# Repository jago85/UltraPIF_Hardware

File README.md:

# UltraPIF_Hardware
The UltraPIF is a replacement for the N64 PIF-NUS chip.

The PIF-NUS chip responsible for region lockout and copy protection. But it also has essential features like game controller access, cartridge EEPROM access and it includes the MIPS CPU boot rom.

The UltraPIF can replace all functions of the original PIF, but ignores the CIC and thus enables a region-free N64. In addition the UltraPIF comes with an integrated clock generator to compensate the differences of the video clocks for NTSC and PAL consoles. The UltraPIF includes an SPI NOR FLASH used to store the N64 software images. At the moment the FLASH is 16 MiB in size and 99% empty, so there could be features like backup and restore of savegame data or even direct emulation of SI (serial interface) hardware (ControllerPak, cart EEPROM, RTC). An RGB LED replaces the original N64 power LED and is used to show if the N64 is running in NTSC or PAL mode. The color is user programmable.

The project consists of custom PCBs, an FPGA design, an MCU firmware and a bunch of software for the N64 itself.

In this repository you find the KiCad hardware files.

You can find hints for assembly and installation in [the wiki](https://github.com/jago85/UltraPIF_Hardware/wiki).

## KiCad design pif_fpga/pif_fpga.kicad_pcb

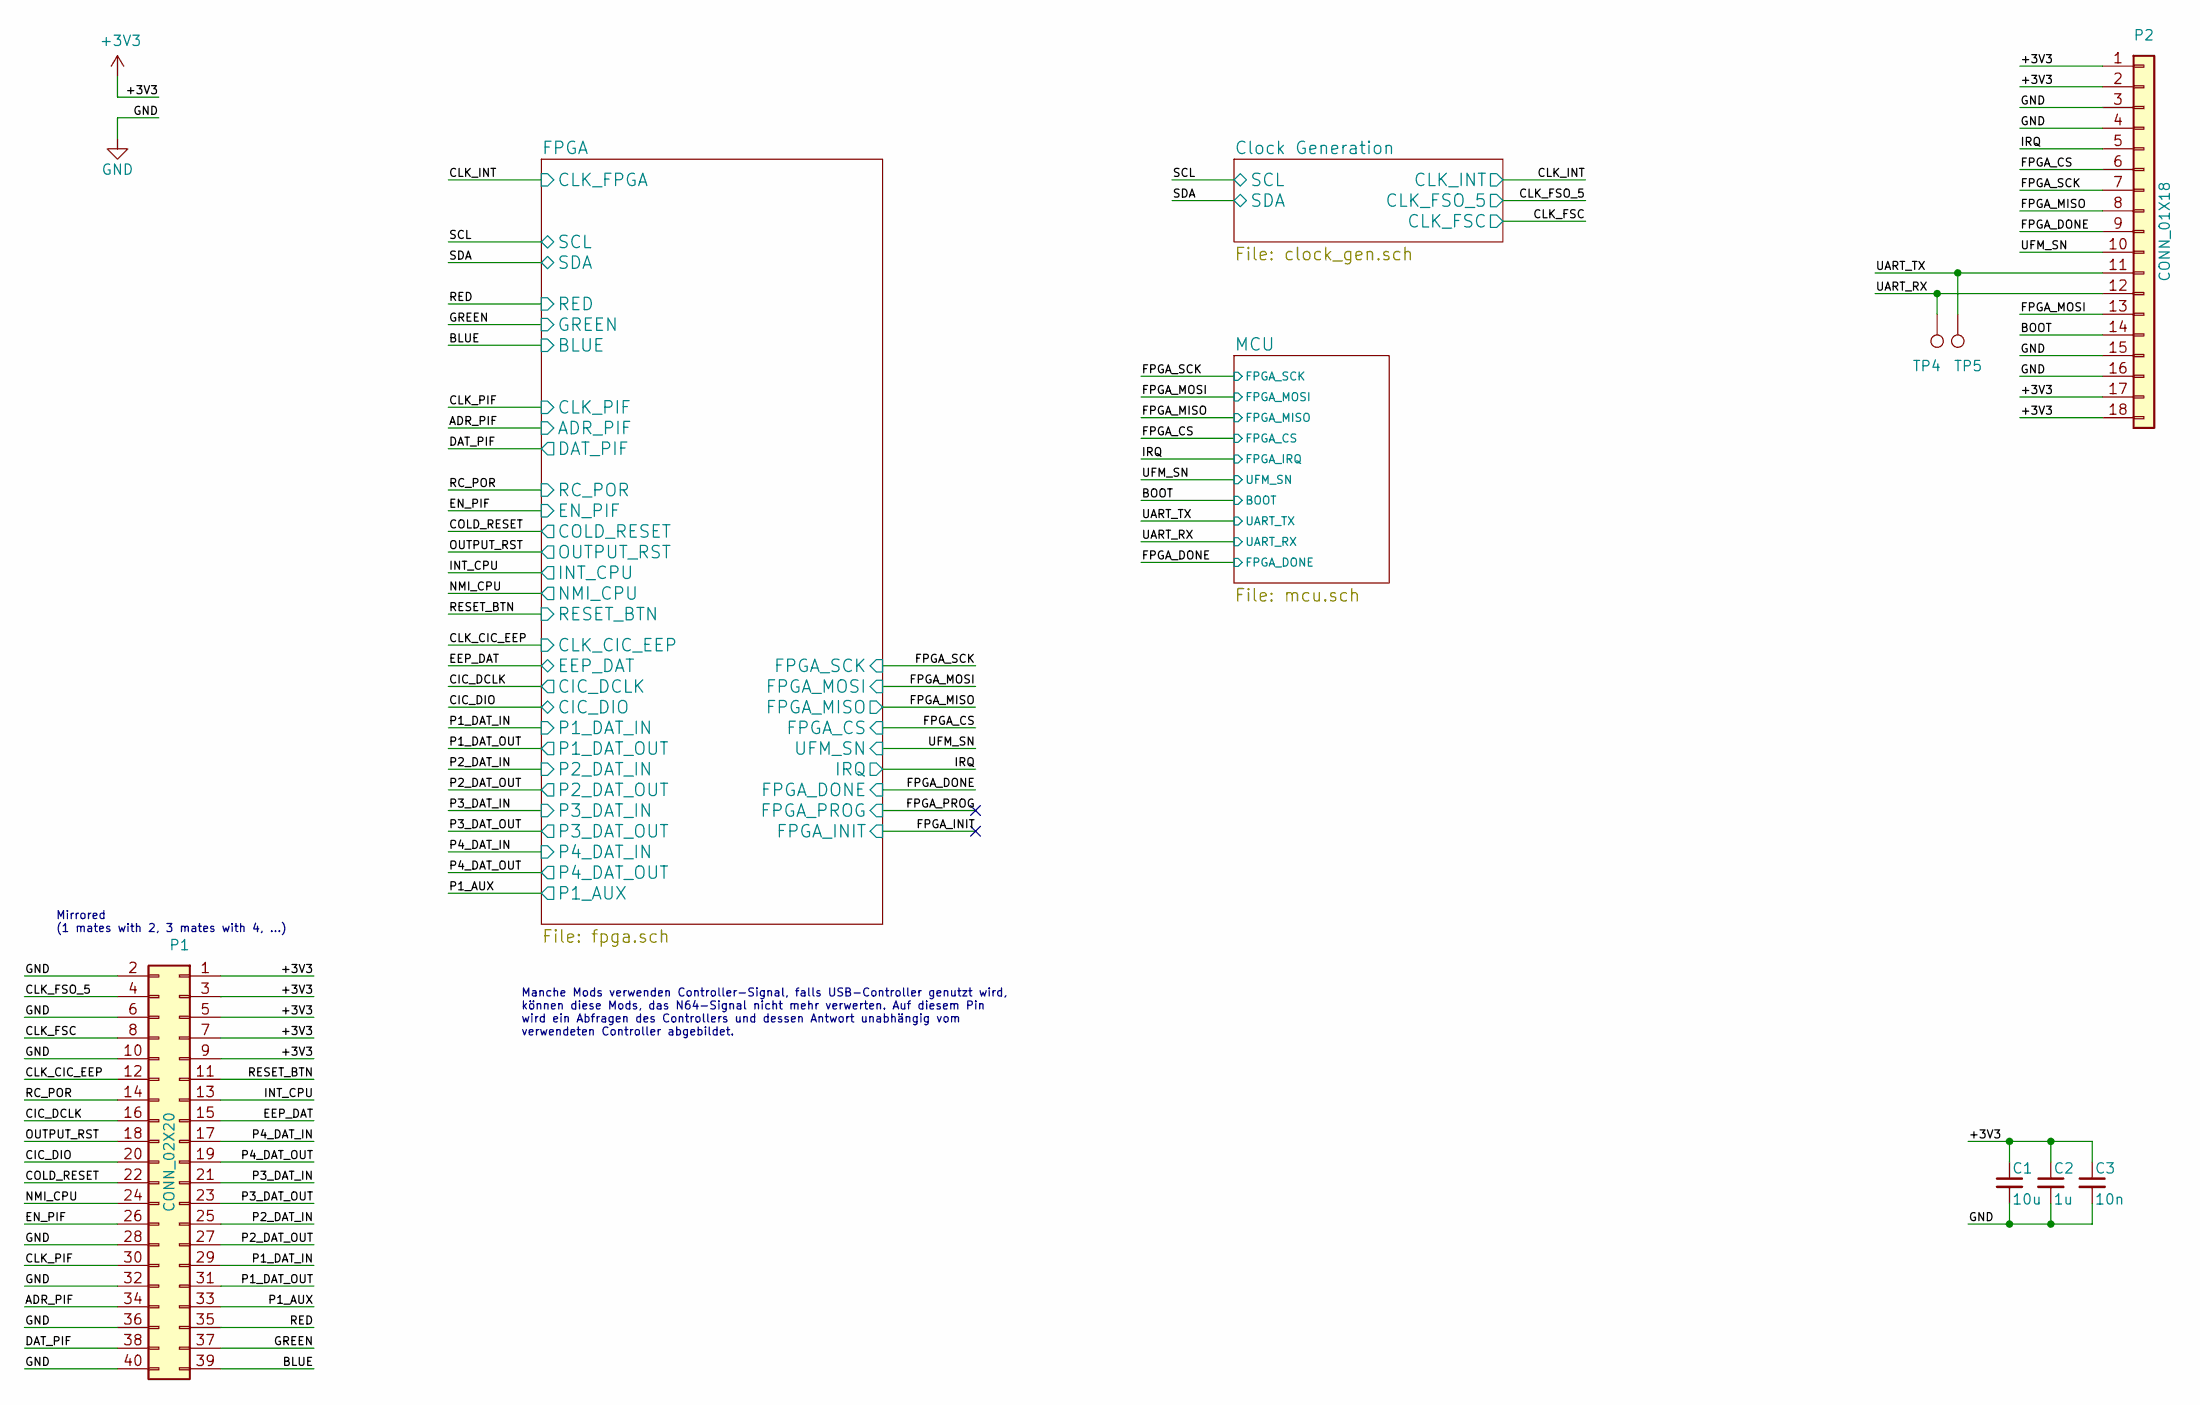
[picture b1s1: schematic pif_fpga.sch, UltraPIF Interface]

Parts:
C1: 10u; C_0805_2012Metric
C2: 1u; C_0603_1608Metric
C3: 10n; C_0603_1608Metric
P1: CONN_02X20; Hirose_DF12A-40DS-0.5V_2x20_P0.50mm_Vertical
P2: CONN_01X18; Molex_BackFlip_18x0.5mm
TP4, TP5: TestPoint; TP_0.8mm

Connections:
+3V3: C1.1, C2.1, C3.1, P1.1, P1.3, P1.5, P1.7, P1.9, P2.1, P2.2, P2.17, P2.18; also elsewhere on the board
/ADR_PIF: P1.34; also elsewhere on the board
/BLUE: P1.39; also elsewhere on the board
/BOOT: P2.14; also elsewhere on the board
/CIC_DCLK: P1.16; also elsewhere on the board
/CIC_DIO: P1.20; also elsewhere on the board
/CLK_CIC_EEP: P1.12; also elsewhere on the board
/CLK_FSC: P1.8; also elsewhere on the board
/CLK_FSO_5: P1.4; also elsewhere on the board
/CLK_PIF: P1.30; also elsewhere on the board
/COLD_RESET: P1.22; also elsewhere on the board
/DAT_PIF: P1.38; also elsewhere on the board
/EEP_DAT: P1.15; also elsewhere on the board
/EN_PIF: P1.26; also elsewhere on the board
/FPGA_CS: P2.6; also elsewhere on the board
/FPGA_DONE: P2.9; also elsewhere on the board
/FPGA_MISO: P2.8; also elsewhere on the board
/FPGA_MOSI: P2.13; also elsewhere on the board
/FPGA_SCK: P2.7; also elsewhere on the board
/GREEN: P1.37; also elsewhere on the board
/INT_CPU: P1.13; also elsewhere on the board
/IRQ: P2.5; also elsewhere on the board
/NMI_CPU: P1.24; also elsewhere on the board
/OUTPUT_RST: P1.18; also elsewhere on the board
/P1_AUX: P1.33; also elsewhere on the board
/P1_DAT_IN: P1.29; also elsewhere on the board
/P1_DAT_OUT: P1.31; also elsewhere on the board
/P2_DAT_IN: P1.25; also elsewhere on the board
/P2_DAT_OUT: P1.27; also elsewhere on the board
/P3_DAT_IN: P1.21; also elsewhere on the board
/P3_DAT_OUT: P1.23; also elsewhere on the board
/P4_DAT_IN: P1.17; also elsewhere on the board
/P4_DAT_OUT: P1.19; also elsewhere on the board
/RC_POR: P1.14; also elsewhere on the board
/RED: P1.35; also elsewhere on the board
/RESET_BTN: P1.11; also elsewhere on the board
/UART_RX: P2.12, TP4.1; also elsewhere on the board
/UART_TX: P2.11, TP5.1; also elsewhere on the board
/UFM_SN: P2.10; also elsewhere on the board
GND: C1.2, C2.2, C3.2, P1.2, P1.6, P1.10, P1.28, P1.32, P1.36, P1.40, P2.3, P2.4, P2.15, P2.16; also elsewhere on the board

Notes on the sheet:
Mirrored (1 mates with 2, 3 mates with 4, ...)
Manche Mods verwenden Controller-Signal, falls USB-Controller genutzt wird, können diese Mods, das N64-Signal nicht mehr verwerten. Auf diesem Pin wird ein Abfragen des Controllers und dessen Antwort unabhängig vom verwendeten Controller abgebildet.

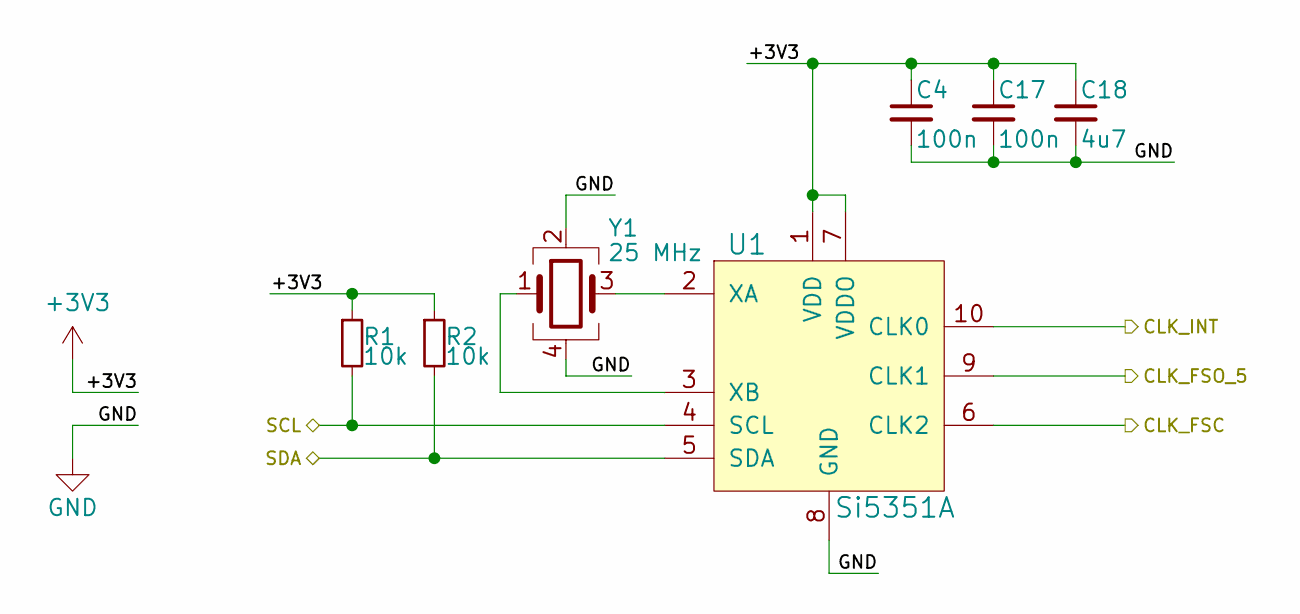
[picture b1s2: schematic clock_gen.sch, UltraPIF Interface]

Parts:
C4, C17: 100n; C_0603_1608Metric
C18: 4u7; C_0603_1608Metric
R1, R2: 10k; R_0603_1608Metric
U1: Si5351A; MSOP-10_3x3mm_P0.5mm
Y1: 25 MHz; Crystal_SMD_3225-4Pin_3.2x2.5mm

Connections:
+3V3: C4.1, C17.1, C18.1, R1.1, R2.1, U1.1 (VDD), U1.7 (VDDO); also elsewhere on the board
/CLK_FSC: U1.6 (CLK2); also elsewhere on the board
/CLK_FSO_5: U1.9 (CLK1); also elsewhere on the board
/CLK_INT: U1.10 (CLK0); also elsewhere on the board
/SCL: R1.2, U1.4 (SCL); also elsewhere on the board
/SDA: R2.2, U1.5 (SDA); also elsewhere on the board
GND: C4.2, C17.2, C18.2, U1.8 (GND), Y1.2, Y1.4; also elsewhere on the board
unnamed: U1.2 (XA), Y1.3
unnamed: U1.3 (XB), Y1.1

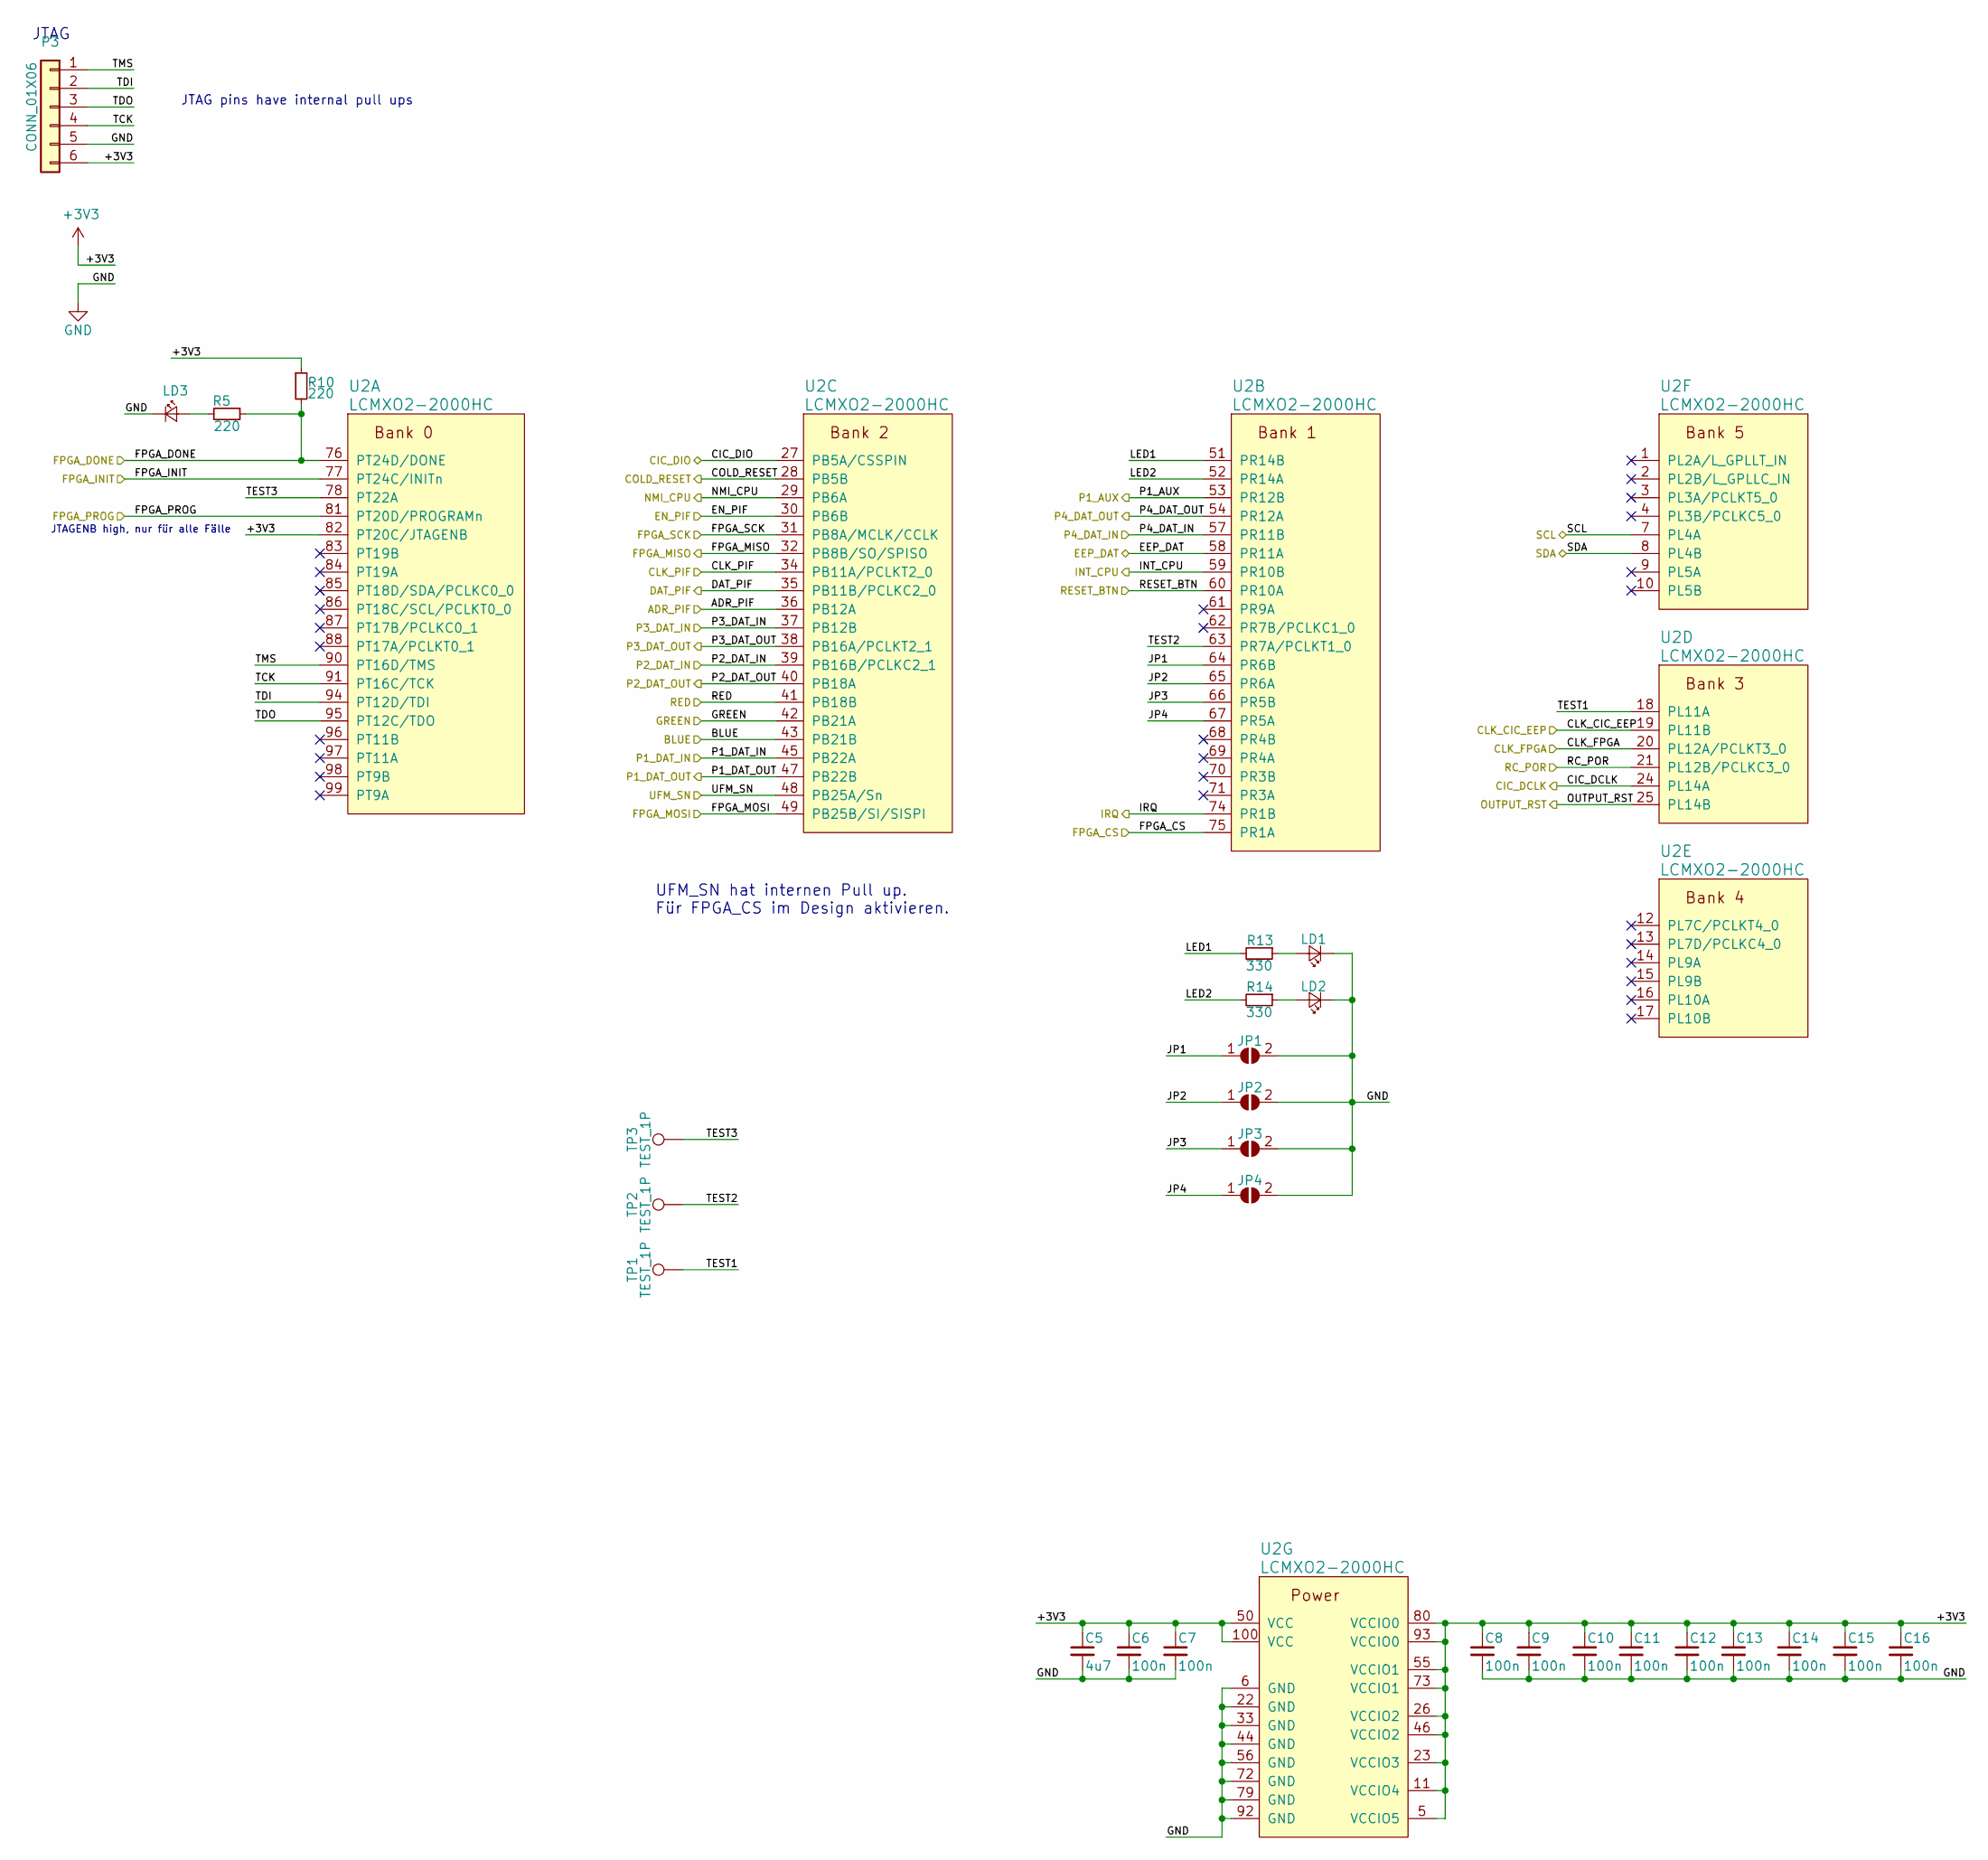
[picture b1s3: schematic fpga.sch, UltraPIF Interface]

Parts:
C5: 4u7; C_0603_1608Metric
C6, C7, C8, C9, C10, C11, C12, C13, C14, C15, C16: 100n; C_0603_1608Metric
JP1, JP2, JP3, JP4: Jumper_NO_Small; SolderJumper-2_P1.3mm_Open_RoundedPad1.0x1.5mm
LD1, LD2, LD3: LED_Small; LED_0603_1608Metric
P3: CONN_01X06; PinHeader_1x06_P2.54mm_NoSolder
R5, R10: 220; R_0603_1608Metric
R13, R14: 330; R_0603_1608Metric
TP1, TP2, TP3: TEST_1P; TP_0.8mm
U2: LCMXO2-2000HC; TQFP-100_14x14mm_P0.5mm

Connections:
+3V3: C5.1, C6.1, C7.1, C8.1, C9.1, C10.1, C11.1, C12.1, C13.1, C14.1, C15.1, C16.1, P3.6, R10.1, U2.5 (VCCIO5), U2.11 (VCCIO4), U2.23 (VCCIO3), U2.26 (VCCIO2), U2.46 (VCCIO2), U2.50 (VCC), U2.55 (VCCIO1), U2.73 (VCCIO1), U2.80 (VCCIO0), U2.82 (PT20C/JTAGENB), U2.93 (VCCIO0), U2.100 (VCC); also elsewhere on the board
/ADR_PIF: U2.36 (PB12A); also elsewhere on the board
/BLUE: U2.43 (PB21B); also elsewhere on the board
/CIC_DCLK: U2.24 (PL14A); also elsewhere on the board
/CIC_DIO: U2.27 (PB5A/CSSPIN); also elsewhere on the board
/CLK_CIC_EEP: U2.19 (PL11B); also elsewhere on the board
/CLK_INT: U2.20 (PL12A/PCLKT3_0); also elsewhere on the board
/CLK_PIF: U2.34 (PB11A/PCLKT2_0); also elsewhere on the board
/COLD_RESET: U2.28 (PB5B); also elsewhere on the board
/DAT_PIF: U2.35 (PB11B/PCLKC2_0); also elsewhere on the board
/EEP_DAT: U2.58 (PR11A); also elsewhere on the board
/EN_PIF: U2.30 (PB6B); also elsewhere on the board
/FPGA/JP1: JP1.1 (A), U2.64 (PR6B)
/FPGA/JP2: JP2.1 (A), U2.65 (PR6A)
/FPGA/JP3: JP3.1 (A), U2.66 (PR5B)
/FPGA/JP4: JP4.1 (A), U2.67 (PR5A)
/FPGA/LED1: R13.2, U2.51 (PR14B)
/FPGA/LED2: R14.2, U2.52 (PR14A)
/FPGA/TCK: P3.4, U2.91 (PT16C/TCK)
/FPGA/TDI: P3.2, U2.94 (PT12D/TDI)
/FPGA/TDO: P3.3, U2.95 (PT12C/TDO)
/FPGA/TEST1: TP1.1, U2.18 (PL11A)
/FPGA/TEST2: TP2.1, U2.63 (PR7A/PCLKT1_0)
/FPGA/TEST3: TP3.1, U2.78 (PT22A)
/FPGA/TMS: P3.1, U2.90 (PT16D/TMS)
/FPGA_CS: U2.75 (PR1A); also elsewhere on the board
/FPGA_DONE: R5.1, R10.2, U2.76 (PT24D/DONE); also elsewhere on the board
/FPGA_MISO: U2.32 (PB8B/SO/SPISO); also elsewhere on the board
/FPGA_MOSI: U2.49 (PB25B/SI/SISPI); also elsewhere on the board
/FPGA_SCK: U2.31 (PB8A/MCLK/CCLK); also elsewhere on the board
/GREEN: U2.42 (PB21A); also elsewhere on the board
/INT_CPU: U2.59 (PR10B); also elsewhere on the board
/IRQ: U2.74 (PR1B); also elsewhere on the board
/NMI_CPU: U2.29 (PB6A); also elsewhere on the board
/OUTPUT_RST: U2.25 (PL14B); also elsewhere on the board
/P1_AUX: U2.53 (PR12B); also elsewhere on the board
/P1_DAT_IN: U2.45 (PB22A); also elsewhere on the board
/P1_DAT_OUT: U2.47 (PB22B); also elsewhere on the board
/P2_DAT_IN: U2.39 (PB16B/PCLKC2_1); also elsewhere on the board
/P2_DAT_OUT: U2.40 (PB18A); also elsewhere on the board
/P3_DAT_IN: U2.37 (PB12B); also elsewhere on the board
/P3_DAT_OUT: U2.38 (PB16A/PCLKT2_1); also elsewhere on the board
/P4_DAT_IN: U2.57 (PR11B); also elsewhere on the board
/P4_DAT_OUT: U2.54 (PR12A); also elsewhere on the board
/RC_POR: U2.21 (PL12B/PCLKC3_0); also elsewhere on the board
/RED: U2.41 (PB18B); also elsewhere on the board
/RESET_BTN: U2.60 (PR10A); also elsewhere on the board
/SCL: U2.7 (PL4A); also elsewhere on the board
/SDA: U2.8 (PL4B); also elsewhere on the board
/UFM_SN: U2.48 (PB25A/Sn); also elsewhere on the board
GND: C5.2, C6.2, C7.2, C8.2, C9.2, C10.2, C11.2, C12.2, C13.2, C14.2, C15.2, C16.2, JP1.2 (B), JP2.2 (B), JP3.2 (B), JP4.2 (B), LD1.1 (K), LD2.1 (K), LD3.1 (K), P3.5, U2.6 (GND), U2.22 (GND), U2.33 (GND), U2.44 (GND), U2.56 (GND), U2.72 (GND), U2.79 (GND), U2.92 (GND); also elsewhere on the board
unnamed: LD1.2 (A), R13.1
unnamed: LD2.2 (A), R14.1
unnamed: LD3.2 (A), R5.2

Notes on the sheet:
JTAG
UFM_SN hat internen Pull up. Für FPGA_CS im Design aktivieren.
JTAGENB high, nur für alle Fälle
JTAG pins have internal pull ups

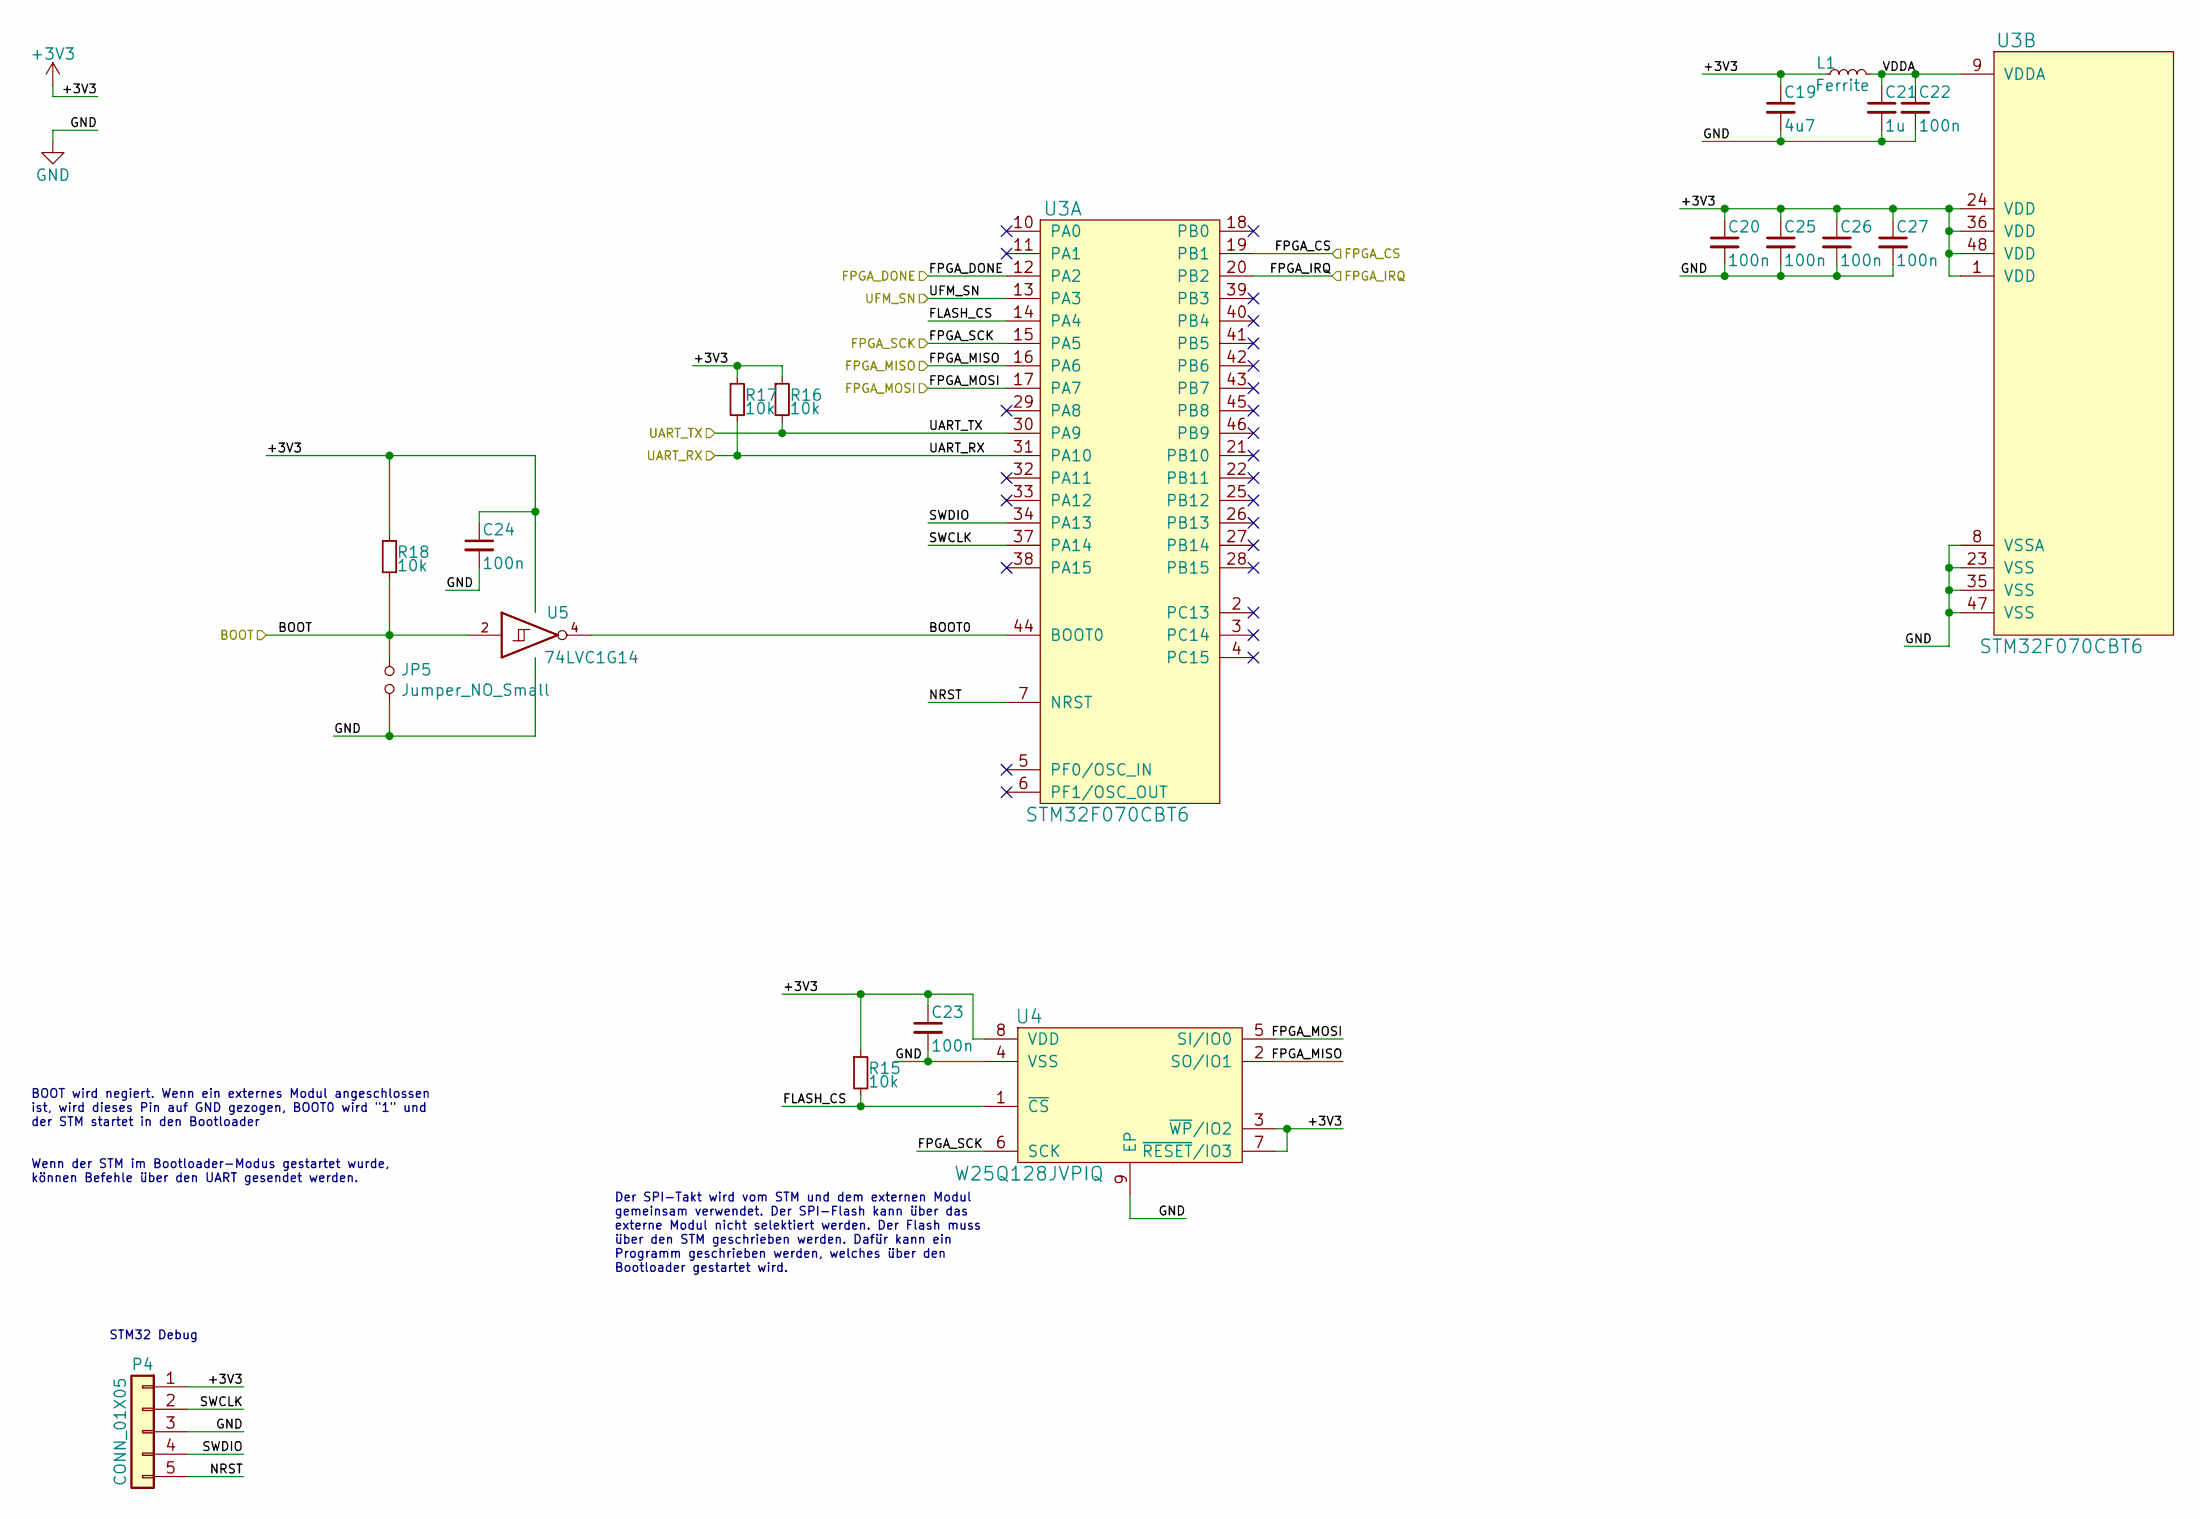
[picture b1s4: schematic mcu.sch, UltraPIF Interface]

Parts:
C19: 4u7; C_0603_1608Metric
C20, C23, C24, C25, C26, C27: 100n; C_0402_1005Metric
C21: 1u; C_0603_1608Metric
C22: 100n; C_0603_1608Metric
JP5: Jumper_NO_Small; SolderJumper-2_P1.3mm_Open_RoundedPad1.0x1.5mm
L1: Ferrite; L_0603_1608Metric
P4: CONN_01X05; PinHeader_1x05_P2.54mm_NoSolder
R15, R16, R17, R18: 10k; R_0603_1608Metric
U3: STM32F070CBT6; LQFP-48_7x7mm_P0.5mm
U4: W25Q128JVPIQ; DFN-8-1EP_6x5mm_P1.27mm_EP2x2mm
U5: 74LVC1G14; SOT-353_SC-70-5

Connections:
+3V3: C19.1, C20.1, C23.1, C24.1, C25.1, C26.1, C27.1, L1.1, P4.1, R15.1, R16.1, R17.1, R18.1, U3.1 (VDD), U3.24 (VDD), U3.36 (VDD), U3.48 (VDD), U4.3 (~WP~/IO2), U4.7 (~RESET~/IO3), U4.8 (VDD), U5.5 (VCC); also elsewhere on the board
/BOOT: JP5.1, R18.2, U5.2; also elsewhere on the board
/FPGA_CS: U3.19 (PB1); also elsewhere on the board
/FPGA_DONE: U3.12 (PA2); also elsewhere on the board
/FPGA_MISO: U3.16 (PA6), U4.2 (SO/IO1); also elsewhere on the board
/FPGA_MOSI: U3.17 (PA7), U4.5 (SI/IO0); also elsewhere on the board
/FPGA_SCK: U3.15 (PA5), U4.6 (SCK); also elsewhere on the board
/IRQ: U3.20 (PB2); also elsewhere on the board
/MCU/BOOT0: U3.44 (BOOT0), U5.4
/MCU/FLASH_CS: R15.2, U3.14 (PA4), U4.1 (~CS)
/MCU/NRST: P4.5, U3.7 (NRST)
/MCU/SWCLK: P4.2, U3.37 (PA14)
/MCU/SWDIO: P4.4, U3.34 (PA13)
/MCU/VDDA: C21.1, C22.1, L1.2, U3.9 (VDDA)
/UART_RX: R17.2, U3.31 (PA10); also elsewhere on the board
/UART_TX: R16.2, U3.30 (PA9); also elsewhere on the board
/UFM_SN: U3.13 (PA3); also elsewhere on the board
GND: C19.2, C20.2, C21.2, C22.2, C23.2, C24.2, C25.2, C26.2, C27.2, JP5.2, P4.3, U3.8 (VSSA), U3.23 (VSS), U3.35 (VSS), U3.47 (VSS), U4.4 (VSS), U4.9 (EP), U5.3 (GND); also elsewhere on the board

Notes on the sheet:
STM32 Debug
Wenn der STM im Bootloader-Modus gestartet wurde, können Befehle über den UART gesendet werden.
Der SPI-Takt wird vom STM und dem externen Modul gemeinsam verwendet. Der SPI-Flash kann über das externe Modul nicht selektiert werden. Der Flash muss über den STM geschrieben werden. Dafür kann ein Programm geschrieben werden, welches über den Bootloader gestartet wird.
BOOT wird negiert. Wenn ein externes Modul angeschlossen ist, wird dieses Pin auf GND gezogen, BOOT0 wird "1" und der STM startet in den Bootloader

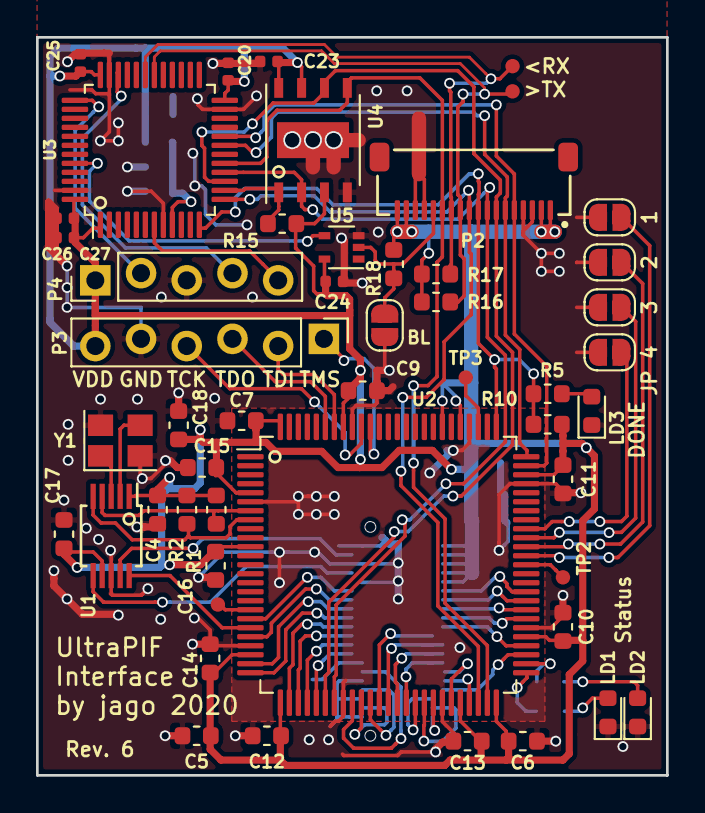
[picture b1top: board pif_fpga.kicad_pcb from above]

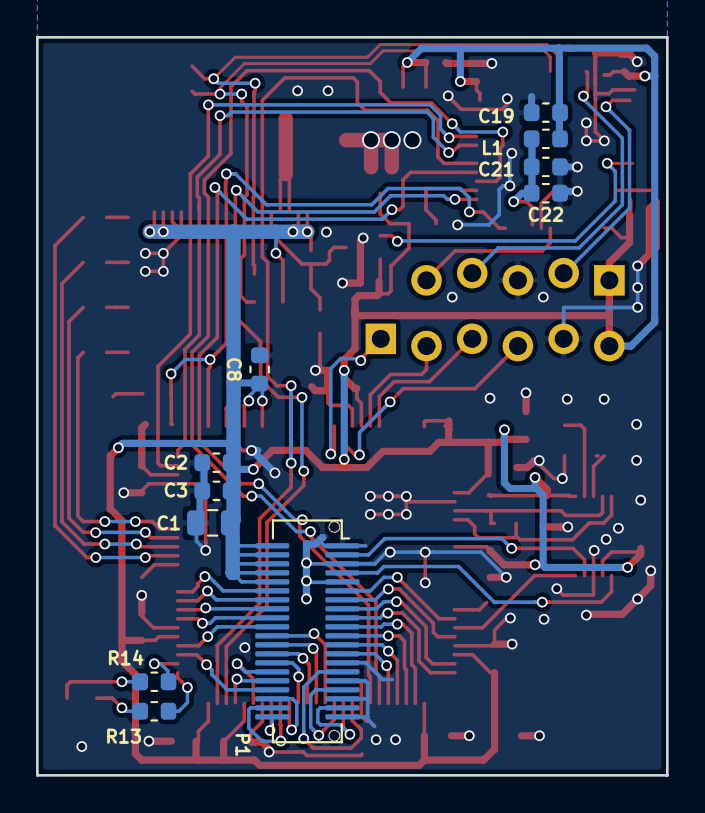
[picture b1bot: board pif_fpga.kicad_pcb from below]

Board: 2 copper layers, 35.0 x 41.0 mm, 61 parts (11 on the bottom side), 67 nets.

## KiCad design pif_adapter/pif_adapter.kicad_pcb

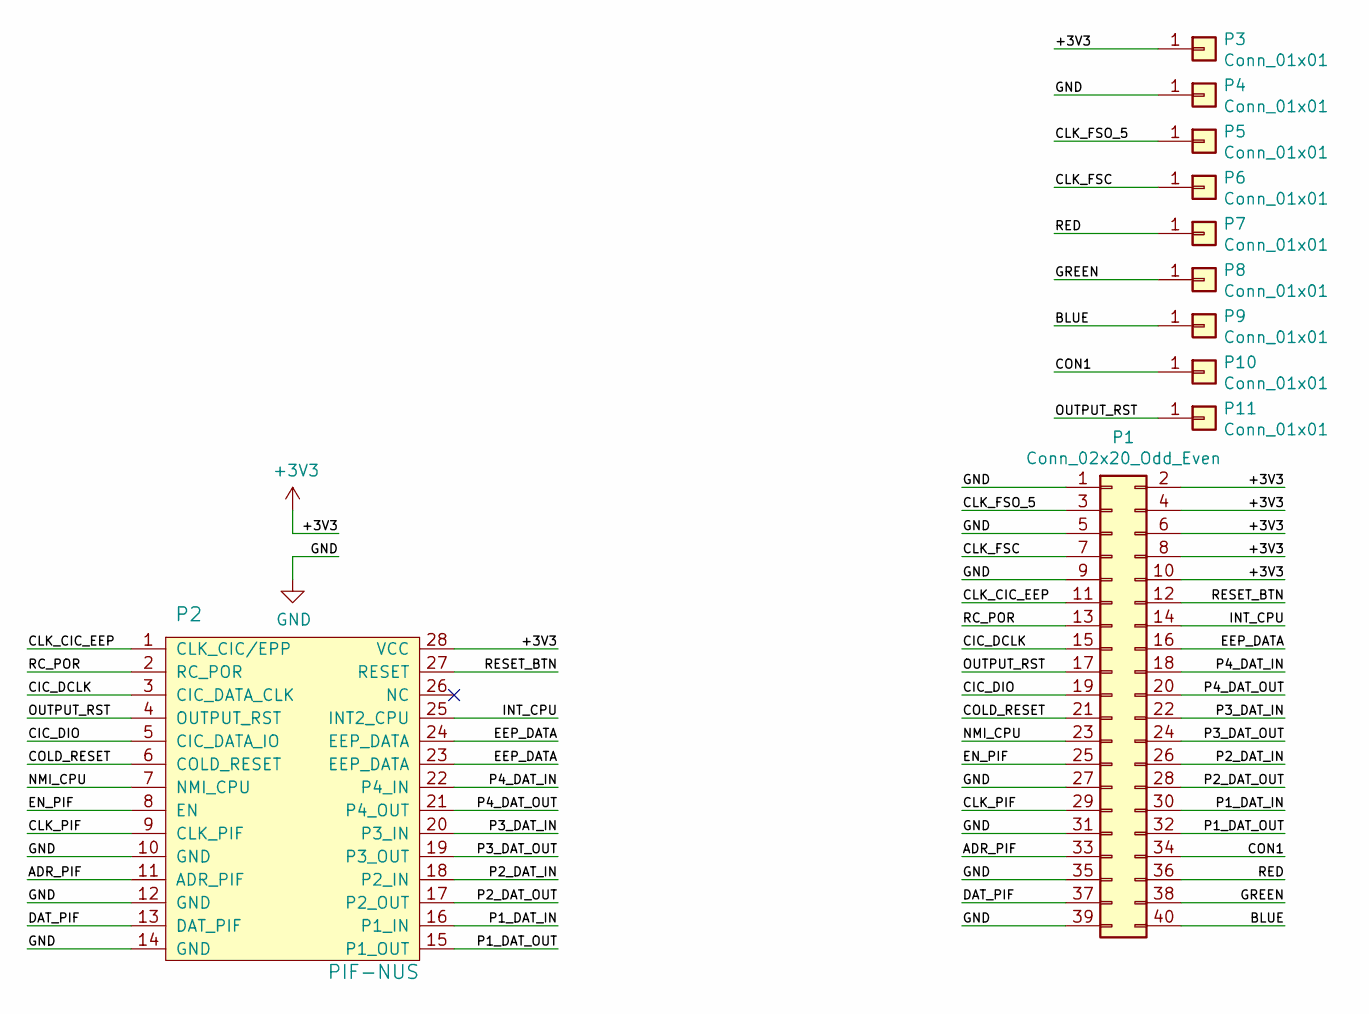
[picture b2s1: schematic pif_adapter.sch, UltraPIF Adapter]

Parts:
P1: Conn_02x20_Odd_Even; Amphenol_MezzoStak-10106813_2x20x0.5mm
P2: PIF-NUS; SOIC28_11mm-Width_Solder_Adapter
P3, P4, P5, P6: Conn_01x01; SolderWirePad_1x01_SMD_1x2mm
P7, P8, P9, P10, P11: Conn_01x01; SolderWirePad_1x01_SMD_0.8x1.3mm

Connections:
+3V3: P1.2, P1.4, P1.6, P1.8, P1.10, P2.28 (VCC), P3.1
/ADR_PIF: P1.33, P2.11 (ADR_PIF)
/BLUE: P1.40, P9.1
/CIC_DCLK: P1.15, P2.3 (CIC_DATA_CLK)
/CIC_DIO: P1.19, P2.5 (CIC_DATA_IO)
/CLK_CIC_EEP: P1.11, P2.1 (CLK_CIC/EPP)
/CLK_FSC: P1.7, P6.1
/CLK_FSO_5: P1.3, P5.1
/CLK_PIF: P1.29, P2.9 (CLK_PIF)
/COLD_RESET: P1.21, P2.6 (COLD_RESET)
/CON1: P1.34, P10.1
/DAT_PIF: P1.37, P2.13 (DAT_PIF)
/EEP_DATA: P1.16, P2.23 (EEP_DATA), P2.24 (EEP_DATA)
/EN_PIF: P1.25, P2.8 (EN)
/GREEN: P1.38, P8.1
/INT_CPU: P1.14, P2.25 (INT2_CPU)
/NMI_CPU: P1.23, P2.7 (NMI_CPU)
/OUTPUT_RST: P1.17, P2.4 (OUTPUT_RST), P11.1
/P1_DAT_IN: P1.30, P2.16 (P1_IN)
/P1_DAT_OUT: P1.32, P2.15 (P1_OUT)
/P2_DAT_IN: P1.26, P2.18 (P2_IN)
/P2_DAT_OUT: P1.28, P2.17 (P2_OUT)
/P3_DAT_IN: P1.22, P2.20 (P3_IN)
/P3_DAT_OUT: P1.24, P2.19 (P3_OUT)
/P4_DAT_IN: P1.18, P2.22 (P4_IN)
/P4_DAT_OUT: P1.20, P2.21 (P4_OUT)
/RC_POR: P1.13, P2.2 (RC_POR)
/RED: P1.36, P7.1
/RESET_BTN: P1.12, P2.27 (RESET)
GND: P1.1, P1.5, P1.9, P1.27, P1.31, P1.35, P1.39, P2.10 (GND), P2.12 (GND), P2.14 (GND), P4.1

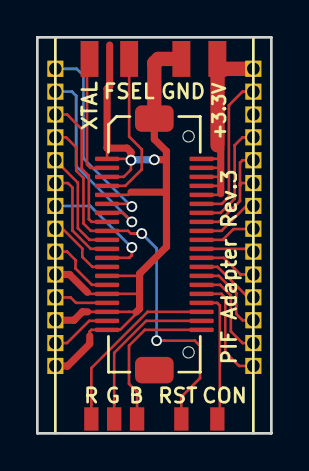
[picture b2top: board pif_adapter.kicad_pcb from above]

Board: 2 copper layers, 13.0 x 22.0 mm, 11 parts (0 on the bottom side), 30 nets.

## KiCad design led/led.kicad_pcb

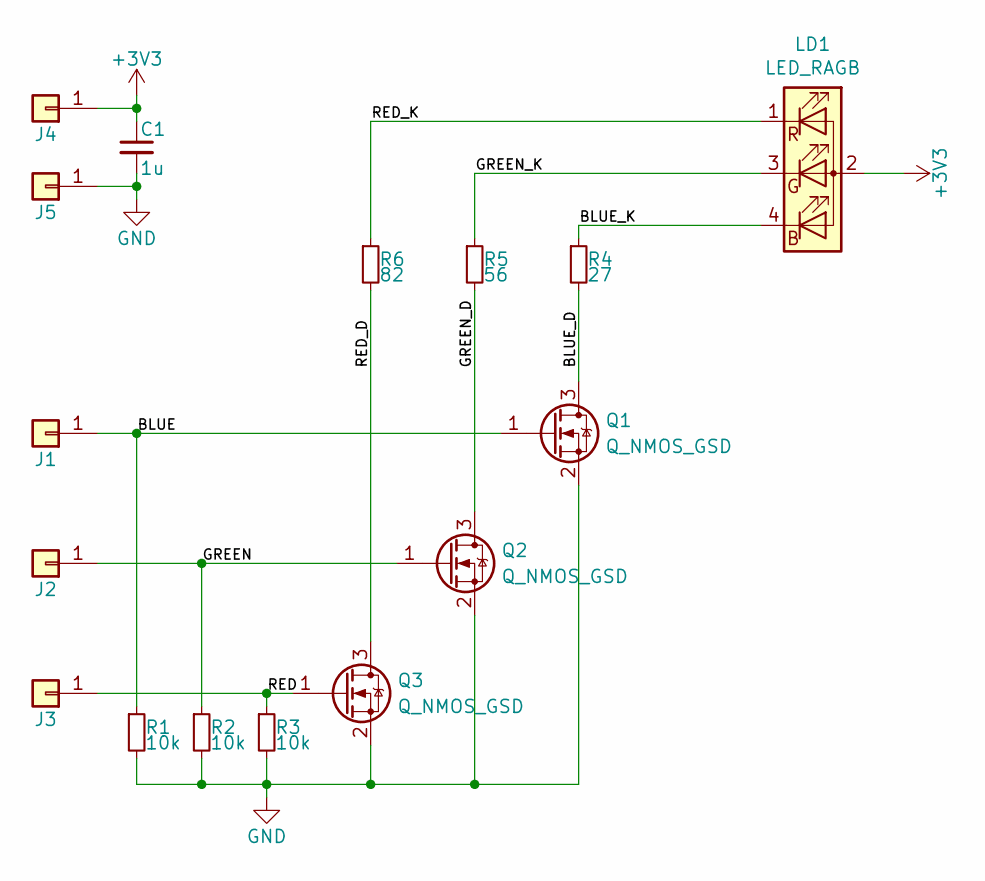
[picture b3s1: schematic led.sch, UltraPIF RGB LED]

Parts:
C1: 1u; C_0603_1608Metric
J1, J2, J3: CONN_01X01; SolderWirePad_1x01_SMD_0.8x1.3mm
J4, J5: CONN_01X01; SolderWirePad_1x01_Drill0.8mm
LD1: LED_RAGB; LED_D5.0mm-4_RGB
Q1, Q2, Q3: Q_NMOS_GSD; SOT-23
R1, R2, R3: 10k; R_0603_1608Metric
R4: 27; R_0603_1608Metric
R5: 56; R_0603_1608Metric
R6: 82; R_0603_1608Metric

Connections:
+3V3: C1.1, J4.1, LD1.2 (A)
/BLUE: J1.1, Q1.1 (G), R1.1
/BLUE_D: Q1.3 (D), R4.2
/BLUE_K: LD1.4 (BK), R4.1
/GREEN: J2.1, Q2.1 (G), R2.1
/GREEN_D: Q2.3 (D), R5.2
/GREEN_K: LD1.3 (GK), R5.1
/RED: J3.1, Q3.1 (G), R3.1
/RED_D: Q3.3 (D), R6.2
/RED_K: LD1.1 (RK), R6.1
GND: C1.2, J5.1, Q1.2 (S), Q2.2 (S), Q3.2 (S), R1.2, R2.2, R3.2

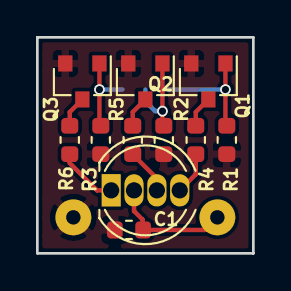
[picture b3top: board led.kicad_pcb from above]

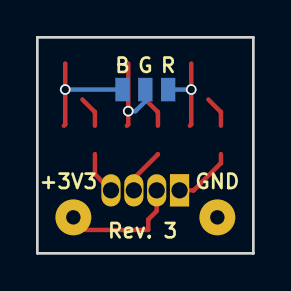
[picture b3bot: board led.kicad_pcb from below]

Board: 2 copper layers, 12.0 x 12.0 mm, 16 parts (3 on the bottom side), 11 nets.
